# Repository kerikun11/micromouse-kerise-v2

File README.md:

# MicroMouse KERISE v2

クラッシクサイズおよびハーフサイズ兼用マイクロマウス

## 戦績

なし

## スペック

| 部品             | 型番            | 備考                    |
| :--------------- | :-------------- | :---------------------- |
| モーター         | 1717T006SR      | 17mm x 17mm             |
| エンコーダ       | IEH2-1024       | 1024パルス モーター直結 |
| マイコン         | STM32F405RG     | 168MHz                  |
| 赤外線LED        | VSLY5850        | 波長850mm 直径5mm       |
| フォトダイオード | SFH213FA        | 波長900nm 直径5mm       |
| モータードライバ | DRV8835         | 最大電流3A              |
| 6軸センサ        | MPU6500         | 3軸ジャイロ+3軸加速度   |
| バッテリー       | LG325-0120-1S-M | 3.7V 25C 120mAh 1S      |

## 回路設計

- KiCad

## 開発環境

- mbed RTOS

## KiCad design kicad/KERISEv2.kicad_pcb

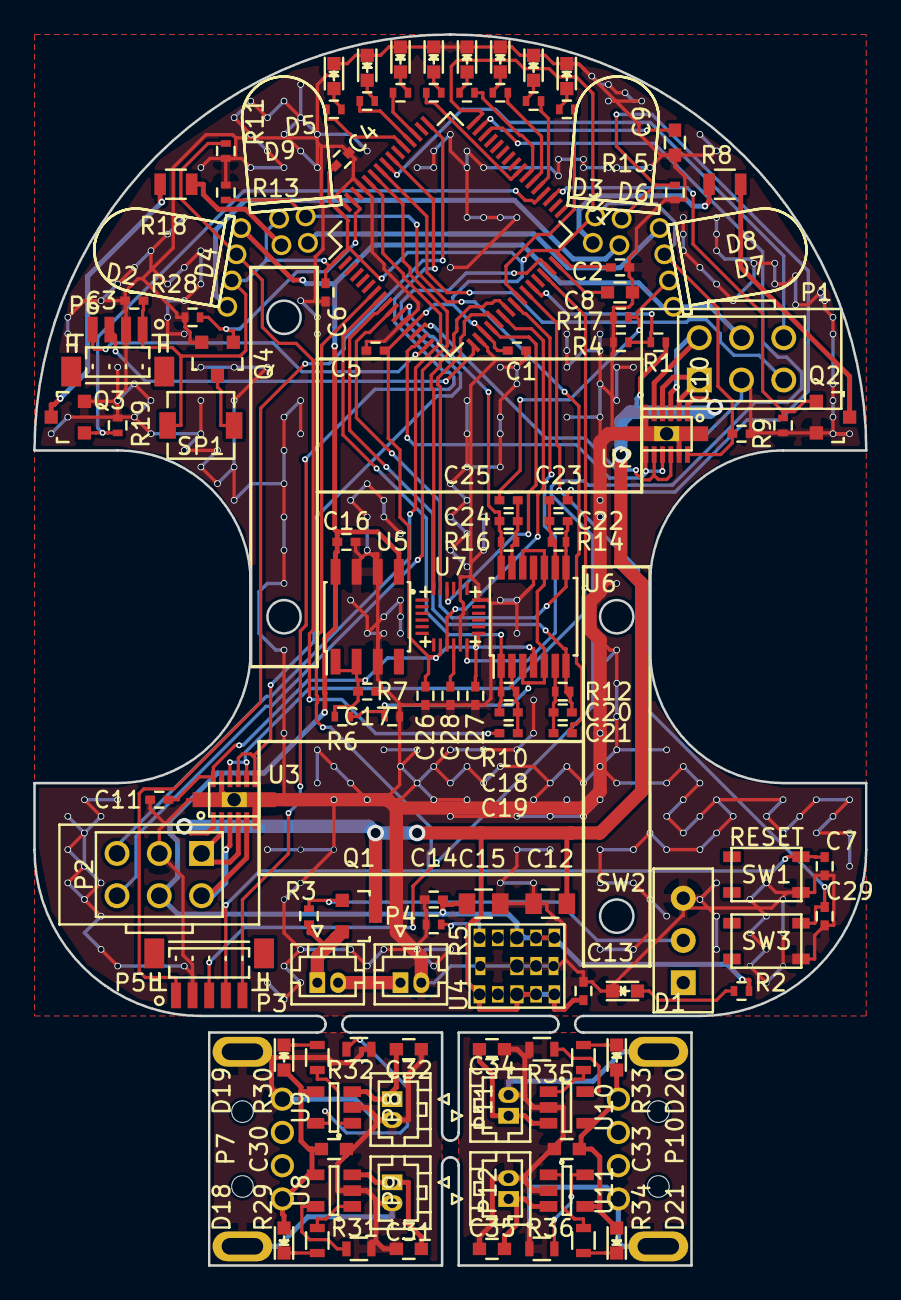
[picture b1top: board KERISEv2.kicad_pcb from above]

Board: 2 copper layers, 50.0 x 74.0 mm, 123 parts (0 on the bottom side), 96 nets.

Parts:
C1, C2, C3, C4, C5, C6, C7, C10, C11, C13, C14, C16, C17, C27, C28, C29: 0.1u; C_0402
C8, C9: 2.2u; C_0603
C12, C15: 22u; C_0805
C18, C20, C22, C24: 22p; C_0402
C19, C21, C23, C25, C26: 0.01u; C_0402
C30, C31, C32, C33, C34, C35: 4.7u; C_0603
D1: Power; LED_0603
D2, D8: VSLY5850; LED-5MM_Angle_wide
D3, D9: VSLY5850; LED-5MM_Angle
D4, D5, D6, D7: SFH213FA; Photo-5MM_Angle
D10, D11, D12, D13, D14, D15, D16, D17, D18, D19, D20, D21: LED; LED_0603
P1, P2: MT-ENC; 1717
P3: Battery_A; Hirose_DF13-02P-1.25DSA_02x1.25mm_Straight
P4: Battery_B; Hirose_DF13-02P-1.25DSA_02x1.25mm_Straight
P5: SWD; JST_SH_BM05B-SRSS-TB_05x1.00mm_Straight
P6: UART; JST_SH_BM04B-SRSS-TB_04x1.00mm_Straight
P7, P10: USB_A; USB_A_P
P8, P11: BAT1; Hirose_DF13-02P-1.25DSA_02x1.25mm_Straight
P9, P12: BAT2; Hirose_DF13-02P-1.25DSA_02x1.25mm_Straight
Q1: IRLML6402; SOT-23
Q2, Q3: IRFML8244; SOT-23
Q4: BSS138; SOT-23
R1: 20k; R_0402
R2, R3, R4, R9, R19, R28: 10k; R_0402
R5: 133; R_0402
R6, R7, R20, R21, R22, R23, R24, R25, R26, R27: 1k; R_0402
R8, R18: 15; R_0805
R10, R12, R14, R16: 220k; R_0402
R11, R13, R15, R17: 100k; R_0402
R29, R30, R33, R34: 1k; R_0603
R31, R32, R35, R36: 4.7k; R_0603
SP1: SMT-0440; SMT-0440-S-R
SW1: RESET; SW_PUSH
SW2: Power; Slide_SW
SW3: BUTTON; SW_PUSH
U1: STM32F405RGTx; LQFP-64_10x10mm_Pitch0.5mm
U2, U3: DRV8835
U4: LXDC55FAAA-203
U5: LT1963ES8; SOIC-8_3.9x4.9mm_Pitch1.27mm
U6: AD8604; TSSOP-14_4.4x5mm_Pitch0.65mm
U7: MPU6500; QFN-24-1EP_3x3mm_Pitch0.4mm
U8, U9, U10, U11: MCP73831; SOT-23-5

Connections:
+1.65VA: R6.2, R7.1, U6.3, U6.5, U6.10, U6.12
+3V3: C1.1, C2.1, C3.1, C4.1, C5.1, C6.1, C10.1, C11.1, C17.1, C26.1, C27.2, D4.1, D5.1, D6.1, D7.1, P6.1, R6.1, SP1.1, U1.1, U1.13, U1.19, U1.32, U1.48, U1.64, U2.12, U3.12, U5.1, U5.2, U6.4, U7.8, U7.13
+5V: C14.1, C15.1, C16.1, D2.2, D8.2, P1.4, P2.4, R2.1, U4.7, U4.8, U4.9, U5.5, U5.8
+BATT: C12.1, C13.1, Q1.3, R1.1, U2.1, U3.1, U4.1, U4.3, U4.4, U4.5
/AXIS_SENSOR/AXIS_CAP: C28.1, U7.10
/Charger A/OUT_1: C31.1, P8.1, U8.3
/Charger A/OUT_2: C32.1, P9.1, U9.3
/Charger A/VDD: C30.1, D18.2, D19.2, P7.1, U8.4, U9.4
/Charger A/VSS: C30.2, C31.2, C32.2, P7.4, P7.5, P8.2, P9.2, R31.2, R32.2, U8.2, U9.2
/Charger B/OUT_1: C34.1, P11.1, U10.3
/Charger B/OUT_2: C35.1, P12.1, U11.3
/Charger B/VDD: C33.1, D20.2, D21.2, P10.1, U10.4, U11.4
/Charger B/VSS: C33.2, C34.2, C35.2, P10.4, P10.5, P11.2, P12.2, R35.2, R36.2, U10.2, U11.2
/IR_LED_FL_SR/IR_LED_R_to_FET: Q3.3, R18.2
/IR_LED_FL_SR/IR_LED_to_IR_LED: D8.1, D9.2
/IR_LED_FL_SR/IR_LED_to_R: D9.1, R18.1
/IR_LED_SL_FR/IR_LED_R_to_FET: Q2.3, R8.2
/IR_LED_SL_FR/IR_LED_to_IR_LED: D2.1, D3.2
/IR_LED_SL_FR/IR_LED_to_R: D3.1, R8.1
/Motor_L/MT_OUT_1: P1.1, U2.2, U2.4
/Motor_L/MT_OUT_2: P1.2, U2.3, U2.5
/Motor_R/MT_OUT_1: P2.1, U3.2, U3.4
/Motor_R/MT_OUT_2: P2.2, U3.3, U3.5
/Power/BAT_to_BAT: P3.2, P4.1
/Power/BAT_to_FET: P3.1, Q1.2, R3.1
AXIS_INT: U1.24, U7.12
AXIS_MISO: U1.22, U7.9
AXIS_MOSI: U1.23, U7.24
AXIS_SCK: U1.21, U7.23
AXIS_~CS: U1.20, U7.22
BAT-VOL: R1.2, R4.1, U1.27
BUTTON: C29.1, SW3.2, U1.26
EN-L-A: P1.6, U1.56
EN-L-B: P1.5, U1.57
EN-R-A: P2.6, U1.58
EN-R-B: P2.5, U1.59
GND: C1.2, C2.2, C3.2, C4.2, C5.2, C6.2, C7.2, C8.2, C9.2, C10.2, C11.2, C12.2, C13.2, C14.2, C15.2, C16.2, C17.2, C26.2, C27.1, C28.2, C29.2, D1.1, D10.1, D11.1, D12.1, D13.1, D14.1, D15.1, D16.1, D17.1, P1.3, P2.3, P4.2, P5.2, P6.2, Q2.2, Q3.2, Q4.2, R4.2, R5.2, R7.2, R9.2, R11.2, R13.2, R15.2, R17.2, R19.2, R28.2, SW1.4, SW2.3, SW3.4, U1.12, U1.18, U1.60, U1.63, U2.6, U2.11, U2.13, U3.6, U3.11, U3.13, U4.6, U4.12, U4.13, U4.14, U5.3, U5.6, U5.7, U6.11, U7.11, U7.18, U7.20
LED_1: R20.1, U1.25
LED_2: R21.1, U1.37
LED_3: R22.1, U1.38
LED_4: R23.1, U1.39
LED_5: R24.1, U1.40
LED_6: R25.1, U1.51
LED_7: R26.1, U1.52
LED_8: R27.1, U1.53
MT-IN-L-1: U1.14, U2.8, U2.10
MT-IN-L-2: U1.15, U2.7, U2.9
MT-IN-R-1: U1.29, U3.8, U3.10
MT-IN-R-2: U1.30, U3.7, U3.9
unnamed: C8.1, U1.31
unnamed: C9.1, U1.47
unnamed: C18.2, C19.1, R10.2, U6.2
unnamed: C19.2, D4.2, R11.1
unnamed: C20.2, C21.1, R12.2, U6.6
unnamed: C21.2, D5.2, R13.1
unnamed: C22.2, C23.1, R14.2, U6.9
unnamed: C23.2, D6.2, R15.1
unnamed: C24.2, C25.1, R16.2, U6.13
unnamed: C25.2, D7.2, R17.1
unnamed: D1.2, R2.2
unnamed: D10.2, R20.2
unnamed: D11.2, R21.2
unnamed: D12.2, R22.2
unnamed: D13.2, R23.2
unnamed: D14.2, R24.2
unnamed: D15.2, R25.2
unnamed: D16.2, R26.2
unnamed: D17.2, R27.2
unnamed: D18.1, R29.1
unnamed: D19.1, R30.1
unnamed: D20.1, R33.1
unnamed: D21.1, R34.1
unnamed: Q1.1, R3.2, SW2.2
unnamed: Q4.3, SP1.2
unnamed: R5.1, U4.11
unnamed: R29.2, U8.1
unnamed: R30.2, U9.1
unnamed: R31.1, U8.5
unnamed: R32.1, U9.5
unnamed: R33.2, U10.1
unnamed: R34.2, U11.1
unnamed: R35.1, U10.5
unnamed: R36.1, U11.5
PR-LED-FL_SR: Q3.1, R19.1, U1.36
PR-LED-SL-FR: Q2.1, R9.1, U1.35
PR-RCV-FL: C20.1, R12.1, U1.9, U6.7
PR-RCV-FR: C22.1, R14.1, U1.10, U6.8
PR-RCV-SL: C18.1, R10.1, U1.8, U6.1
PR-RCV-SR: C24.1, R16.1, U1.11, U6.14
RESET: C7.1, P5.4, SW1.2, U1.7
SPEAKER: Q4.1, R28.1, U1.62
SWCLK: P5.1, U1.49
SWDIO: P5.3, U1.46
SWO: P5.5, U1.55
UART-RX: P6.3, U1.17
UART-TX: P6.4, U1.16

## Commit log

2016-11-24 外形を作成
2016-11-24 大きめの部品を配置
2016-11-25 フットプリント調整
2016-11-25 徐々に部品を配置，部品の確認
2016-11-26 とりあえず全部品を配置
2016-11-26 ネットリストとデザインルールを更新
2016-11-27 ネットリストを更新
2016-11-27 IR LEDとフォトダイオードのフットプリントを更新．
    かなりすっきり収まった．
2016-11-30 部品表を作成
2016-11-30 部品の位置を調整，ロゴを貼り付け
2016-12-01 自動配線へ出力
2016-12-02 リポ充電基板を追加
2016-12-02 充電基板を階層に．
2016-12-02 自動配線Postroute
2016-12-03 自動配線結果を反映
2016-12-03 viaを量産
2016-12-03 ガーバーを生成
2016-12-03 ファイル名を変更，整理
2016-12-03 基板発注
2016-12-06 基板やマウンタの画像を追加
2016-12-18 MicroMouse2016のfirmwareを移植
2016-12-20 PIパラメータの調整，ログの出力
2016-12-20 ログの解除
2016-12-21 MPU6500の読み取り部分を整理．6軸を読み取り．
2016-12-21 PIDパラメータを再調整
2016-12-22 WallAttachのバグ修正
    x修正時に回転するのを忘れていた．
2016-12-23 PCなしでジグザグなどのデモを行えるようにした
2016-12-24 MPUを台形積分
2016-12-25 積分とキャリブレーションのバグを修正，加速度を[mm]単位に変換
2016-12-25 -45度入45度出を実装
2016-12-26 パラメータの調整
2016-12-26 デバック出力を削除
2016-12-26 新基板，部品を配置
2016-12-28 自動配線用にdsn吐き出し
2016-12-28 製造ファイル出力
2017-01-08 新基板用コード移植
    MicroMouse2016より
2017-01-08 PIDパラメータの調整
2017-01-08 MATLABファイルを追加
2017-01-09 壁センサがサチらないように調整
2017-01-09 壁センサの調整
2017-01-09 リフレクタの調整
2017-01-09 サインカーブの軌跡生成
2017-01-10 直線を含まないカーブの生成
2017-01-10 新しい軌跡追従の書き始め
2017-01-10 制御方法を変更
    カーブごとに独立制御
    カーブをつなぐ直線で速度を整える
2017-01-10 サインカーブの角加速度と最大角速度を固定
2017-01-11 角加速度を小さく
2017-01-11 安定走行
2017-01-12 ハーフで探索&最短
    帰りはまだ．
2017-01-12 速度一定の自律走行(クラシック)
2017-01-15 symsを使って軌道生成
2017-01-15 UIを改良
2017-01-17 ハーフで探索&最速
2017-01-17 45度軌道生成
2017-01-19 45度から60度に変更して壁を避ける
2017-01-19 ode45で軌道生成
2017-01-19 横壁補正
2017-01-20 150度カーブを2区画から3区画に変更
    8の字が不可能に．
2017-01-21 探索中の事故に備えて再開可能に
2017-01-21 直線の加速を3次曲線に．
    安定走行
2017-01-22 探索中，次の行き先が決まるまで止まるように変更
2017-01-24 起動時にクラッシュするバグを修正
    リフレクタのキャリブレーションに失敗していた
2018-08-13 submodule add mbed-os-kerise
2020-05-02 add gitignore
